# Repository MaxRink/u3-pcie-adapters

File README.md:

# U.3 PCIe adapters

Passive, PCIe 4.0 adapters for U.3 (SFF-TA-1001) NVMe drives, built around HPE P50230-B21 /
Samsung PM1735a drives that refuse U.2-wired hosts. KiCad projects, fabbed at JLCPCB or PCBWay.

## Designs

| Design | Boards | Status |
| --- | --- | --- |
| [**x16 / x8 U.3 cards**](designs/x16-u3-card/) | x8 card (2 drives), x16 card (4 drives, passive or with retimer), OCuLink cage board | cage board routed and DRC clean; cards in layout |
| [**Minisforum MS-01 / MS-A2**](designs/minisforum-u3/) | U.3-wired x4 card for the PCIe slot, U.3-wired replacement for the M.2 adapter | waiting on measurements of the stock adapters |
| [**Cooling shroud**](docs/thermal/) | 3D-printed high-temp shroud for the Jonsbo N5 | sized from the thermal analysis; model in progress |

<table>
<tr>
<td><br>Cage board, top</td>
<td><br>Cage board, bottom (OCuLink)</td>
</tr>
<tr>
<td><br>x8 card with 2 drives</td>
<td><br>x16 card with 4 drives</td>
</tr>
<tr>
<td><br>CFD: 4 drives x 25 W in line, 30 CFM</td>
<td><br>Hottest drive vs airflow (x8 / x16)</td>
</tr>
</table>

## Cooling in one paragraph

Each drive can draw ~25 W, and on the cards the drives sit in a row, so the air passes them one
after another. With 35 °C air coming in and a 70 °C case limit, the x8 card (2 drives) needs about
20 CFM and the x16 card (4 drives) about 30 CFM at ~150 Pa. That takes a 92x38 mm server-class
fan: it holds 2 drives at ~66 °C and 4 drives at ~71 °C (marginal; 3 mm shroud gaps or a 20 W
drive power state give margin). A 92x25 mm fan is not enough for either. Details, OpenFOAM
results and the calibrated model: [`docs/thermal/`](docs/thermal/).

## Layout

| Path | Contents |
| --- | --- |
| [`design-rules/`](design-rules/) | Shared PCIe 4.0 + JLCPCB/PCBWay rules: stackups, impedance, `.kicad_dru` DRC rules, KiCad starter templates, SI scripts |
| [`designs/x16-u3-card/`](designs/x16-u3-card/) | x16 / x8 slot cards for 2–4 U.3 drives, OCuLink cage board |
| [`designs/minisforum-u3/`](designs/minisforum-u3/) | U.3 adapters for Minisforum MS-01 / MS-A2 (PCIe x4 card, M.2-slot board) |
| [`tools/render/`](tools/render/) | Headless 3D renders of any `.kicad_pcb` (real copper/mask/silk, STEP parts, drives plugged in) |
| [`tools/thermal/`](tools/thermal/) | Analytical airflow/thermal model and OpenFOAM CFD case generator for the drive stack |
| [`docs/`](docs/) | Research notes, renders (`docs/img/`), thermal results (`docs/thermal/`) |

## Conventions

- One folder per design under `designs/`; one KiCad project per board inside it.
- Every board uses a template from `design-rules/templates/` and the custom rules in
  `design-rules/pcie4_jlc_pcbway.kicad_dru`. Change the rules there, not per board.
- Don't commit KiCad backups, `*.kicad_prl`, or fab output zips (see `.gitignore`);
  attach fab outputs to GitHub releases instead.
- Re-render a board after changing it (`tools/render/render.py`) so the README pictures match.

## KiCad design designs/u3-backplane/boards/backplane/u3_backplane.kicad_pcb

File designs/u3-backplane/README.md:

# Cabled U.3 backplane

A small NVMe backplane in the style of a Supermicro CSE-SAS-733TQ: U.3 drives stand on vertical receptacles,
every cable leaves sideways on the underside, and a host card in a PCIe x16 slot feeds it over SlimSAS 8i cables.
It is meant to sit flat in the top compartment of a Jonsbo N5 behind the two front 120 mm fans, with the drives
loaded from the top (so they can be swapped with the lid off), inside a printed cage.

| Board | Size | Drives | Cables | Files |
| --- | --- | --- | --- | --- |
| Backplane, 4 drives | 79.6 x 90.5 mm | 4 | 2 x SlimSAS 8i | `boards/backplane`, `fab/backplane` |
| Backplane, 6 drives | 119.6 x 90.5 mm (one 120 mm fan wide) | 6 | 3 x SlimSAS 8i | `boards/backplane6`, `fab/backplane6` |
| Host card, passive | 131 x 44 mm, PCIe x16 | 4 per card | 2 x SlimSAS 8i | `boards/host_passive`, `fab/host_passive` |

Two 6-drive modules side by side give 12 drives across both fans. That is 48 lanes: six 8i cables and three
x16 slots set to x4x4x4x4 (or a PCIe switch card).

All boards use the project's 6-layer rule set (JLC06161H-3313, 85 ohm pairs 0.157 / 0.152 mm, see
`design-rules/`). They are generated by the scripts in `gen/`; nothing is drawn by hand.

## Mechanics

Drawings: `docs/backplane_mech.svg`, `docs/backplane6_mech.svg`. Board-only STEP models are in `fab/*/`.

- Frame: seen from the drive side, origin top-left, x right, y down.
- Drive receptacles (Amphenol PSAS5F3130021TR, vertical, 8.15 mm tall) at x = 9.8 + 20 * i, y = 48.5, long axis
  along y, 20 mm pitch. Module pitch is 80 / 120 mm with 0.4 mm between boards.
- M3 holes: (3.2, 15.5), (W - 3.2, 15.5) and (36 + 40 * c, 86.3) for every drive pair c.
- Underside (all right angle, tallest part 13 mm, the cage keeps 15 mm clear):
  - y = 90.5 edge: one SlimSAS 8i per drive pair, centred at x = 15.8 + 40 * c.
  - y = 0 edge, left to right from the drive side: fan control in (1x4), 12 V in, 12 V out (Mini-Fit Jr 2x4),
    fan + fan control out (1x8).
- Slots between the drives let air through when the board stands upright. Lying flat they are not needed.

Assumed, not measured: the N5 top compartment has room for the cage (Max: "plenty of space"), and the drive's end
face sits about 6.5 mm above the board. The Amphenol drawing gives the 8.15 mm body height only.

## Electrical design

**Lanes.** One x4 link per drive, no lane crossings and exactly one via per net. Host transmit (PET) runs on L1
and drops to L6 behind the SlimSAS pads, drive transmit (PER) runs on L6. Lanes are 19 to 43 mm long. Pairs are
matched by the position of their vias, without serpentines (largest skew 0.004 mm, see
`fab/*/*-lengths.json`). 220 nF AC caps sit on the drive's lane 0 and 1 transmit pairs only
(SFF-TA-1001), S15 (HPT0) is grounded.

| SlimSAS connector | Port A (pins 1-18, host lanes 0-3) | Port B (pins 19-37, host lanes 4-7) |
| --- | --- | --- |
| first (left) | drive 1 | drive 0 |
| second | drive 3 | drive 2 |
| third (6-drive board) | drive 5 | drive 4 |

Sidebands follow SFF-9402: every port carries its own REFCLK, PERST#, CPRSNT#, CWAKE# and BP_TYPE (pulled low).
Cables must be the crossover type the spec describes (row A at one end is row B at the other).

**Power and hot plug.** 12 V enters on a PCIe 8-pin (Mini-Fit Jr) and is passed on to a second one for the next
module. Each drive has its own TPS259824 eFuse: about 3.9 A limit, soft start (10 nF on dV/dt), and it is only
switched on while a drive is present (PRSNT# or IfDet# low through a 74LVC1G00). A TPS3808 watches the drive's
12 V and releases the drive's PERST# about 125 ms after the rail is good, so a freshly inserted drive always sees
a proper reset. An empty bay is unpowered.

Daisy chain limit: a PCIe 8-pin is specified for 150 W. Four 25 W drives are 100 W, six are 150 W, so chain two
4-drive modules only with drives that stay under about 18 W each, and give every 6-drive module its own lead.

Host side of hot plug: the backplane is electrically safe to plug and pull. Whether the OS notices on its own
depends on the root port. A bifurcated consumer slot normally has no hot-plug slot capability, so use
`echo 1 > /sys/bus/pci/devices/<bdf>/remove` before pulling and `echo 1 > /sys/bus/pci/rescan` after inserting.
Boards that expose "PCIe hot plug" or Intel VMD for the slot handle it without that.

**Management.** One TCA9548A SMBus switch (address 0x71) gives every drive its own channel (channel = drive
number). One TCA9554 per drive pair (0x20, 0x21, 0x22) reads PRSNT#, IfDet#, IfDet2# and drives PWRDIS for both
drives (bits 0-3 even drive, 4-7 odd drive). The upstream bus is the 2-wire pair of port A on the first SlimSAS
connector; that port's PERST# also resets the switch. 3.3 V comes from an on-board LDO fed from 12 V (drive side,
above the fan header). L4 carries 12 V above the drives and to every eFuse and 3.3 V everywhere else.

**Fan.** The 1x8 header's pins 1-4 are a standard 4-pin fan header (GND, 12 V through a 1.1 A PTC, tach, PWM).
PWM and tach come from the "control in" header (mainboard fan header or the previous module), and PWM is passed
on by pins 5-8 to the next module. The 12 V pins of the control headers are not connected, so nothing is fed back
into the mainboard.

## Host card (passive)

PCIe x16 edge to two SlimSAS 8i, for a slot set to x4x4x4x4. The connectors sit on the underside at the top edge,
which keeps the lane order of the fingers. PET has one via, PER two. A 9DBL0442 buffer (bypass mode) gives each
port its own REFCLK, a TCA9546A (0x77) gives each port its own SMBus channel (channel 0 reaches the backplane's
switch), a TCA9554 (0x27) reads CPRSNT# and BP_TYPE of the four ports, PERST# goes to every port through 33 ohm
and the four CWAKE# lines join WAKE#. Trace length is 23 to 30 mm per lane.

A passive card plus a 0.5 m cable plus the backplane (19 to 43 mm) is past what PCIe 4.0 allows without
re-equalisation. Expect Gen3 to work and Gen4 to depend on the board and the cable. For Gen4, use a redriver or
retimer card.

**Redriver and retimer versions: not built (decided 2026-11-13).** For PCIe 4.0 a retimer card is bought instead
(see below). A redriver card (4 x DS160PR810) was analysed but not laid out: it does not re-time, so Gen4 over
0.5 m would stay uncertain. A retimer card cannot be laid out from public data, TI's public DS160PT801 datasheet
has no ball map.

## What to buy

Cables (one per drive pair): SlimSAS SFF-8654 8i to 8i, straight, 85 ohm, "PCIe 4.0", with sidebands, 0.5 m or
shorter.

| Cable | Notes |
| --- | --- |
| 3M 8ES8-1DF21-0.50 | reference-grade twinax, 85 ohm; the safest choice |
| 10Gtek CAB-8654/8654-8i-P-85 | "PCIe 4.0, 85 ohm, with sideband", 0.5 to 1 m, listed at about 15 USD (2026-11-13) |
| Delock 82303 (0.5 m) | SlimSAS 8i to 8i; impedance and sidebands not confirmed from the product page |

Avoid 100 ohm "SAS" cables and cables without sidebands: the drives would get no clock or reset.

Host card to buy instead of building one: a x16 to dual SlimSAS 8i **retimer** card, for example LR-LINK
LRNV9F24 or the C-Payne "SlimSAS PCIe gen4 host adapter x16" in its retimer version. Prices could not be read
from the vendor pages (LR-LINK sells on inquiry). Check before ordering that the card follows SFF-9402 on the
cable side (REFCLK and PERST# on every port); a card that only passes lanes will not bring up the drives.

## Cost estimate (JLCPCB, bare boards)

Not quoted live. Scaled from the project's quotes of 2026-11-13 for the same stackup (6 layers, ENIG, impedance
control, 0.2 mm vias: 141 to 188 USD for 5 to 10 cards of 190 to 310 mm length), where the fixed 6-layer charges
dominate:

| Board | 5 pcs | 10 pcs |
| --- | --- | --- |
| Backplane, 4 drives | about 105 USD | about 115 USD |
| Backplane, 6 drives | about 115 USD | about 130 USD |
| Host card (adds gold fingers and bevel) | about 125 USD | about 140 USD |

Parts per 4-drive backplane are roughly 45 USD (four receptacles about 4 USD each, two SlimSAS about 6 USD each,
four eFuses, the rest small), per host card roughly 30 USD. Shipping and tax are extra.

## Check before ordering

- Pin 1-3 = 12 V on the Mini-Fit Jr footprints was taken from the Molex numbering; check with a PSU cable.
- MCP1703A SOT-223 pinout (VIN, GND, VOUT) and the TPS259824 land pattern split are from memory or inferred.
- eFuse values (390 ohm ILIM, 2.2 nF ITIMER, 10 nF dV/dt) come from the datasheet formulas as remembered.
- LCSC numbers are filled in only where known; empty fields in the BOM need a part chosen.
- The 9DBL0442 and the eFuse are QFNs. Everything else is leaded or 0402 and larger; hot air works for all of it.
- The U.3 receptacle's seated drive height and the connector offset on the drive were not available.

## Regenerating

```
cd designs/u3-backplane/gen
ND=4 python3 bp.py        # 4-drive backplane (ND=6 for six), about 30 min
python3 host.py           # passive host card
cd .. && tools/outputs.sh backplane u3_backplane "Cabled U.3 backplane, 4 drives"        # backplane6 / u3_backplane6 for six
```

`tools/outputs.sh` runs the DRC (`tools/drc.py`) and writes the Gerber zip, BOM, CPL, the board-only STEP, the lane
length report and the mechanical drawing.

`STAGE=place` skips the low-speed router and gives a placement DRC in seconds. KiCad 7.0.11. A full run takes 20 to 30
minutes per board.

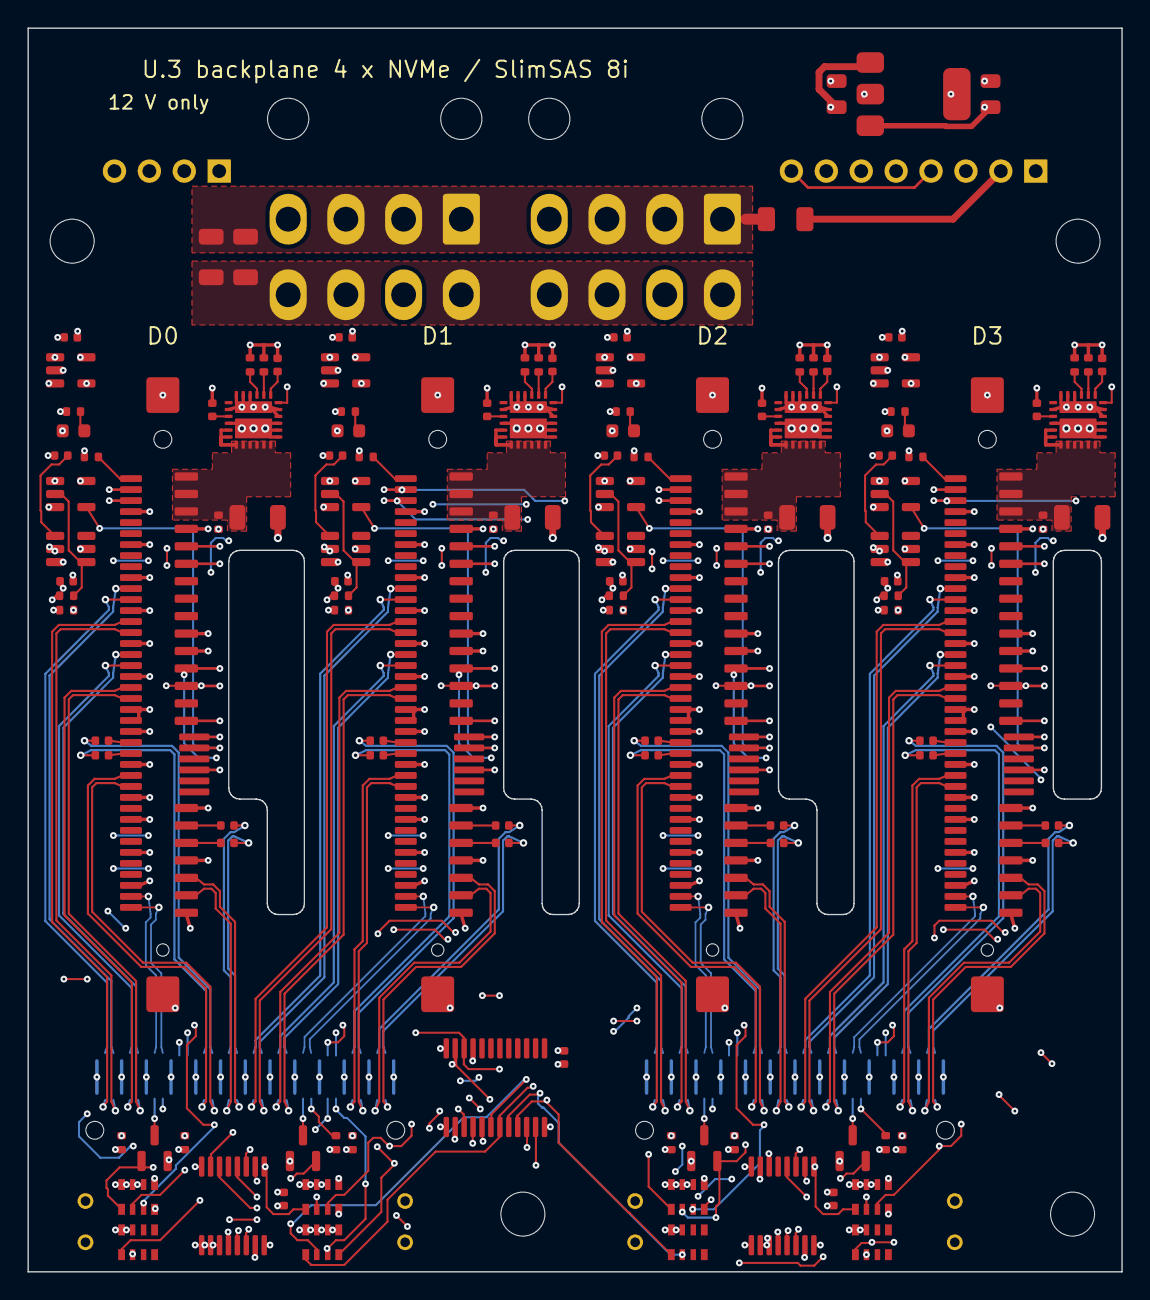
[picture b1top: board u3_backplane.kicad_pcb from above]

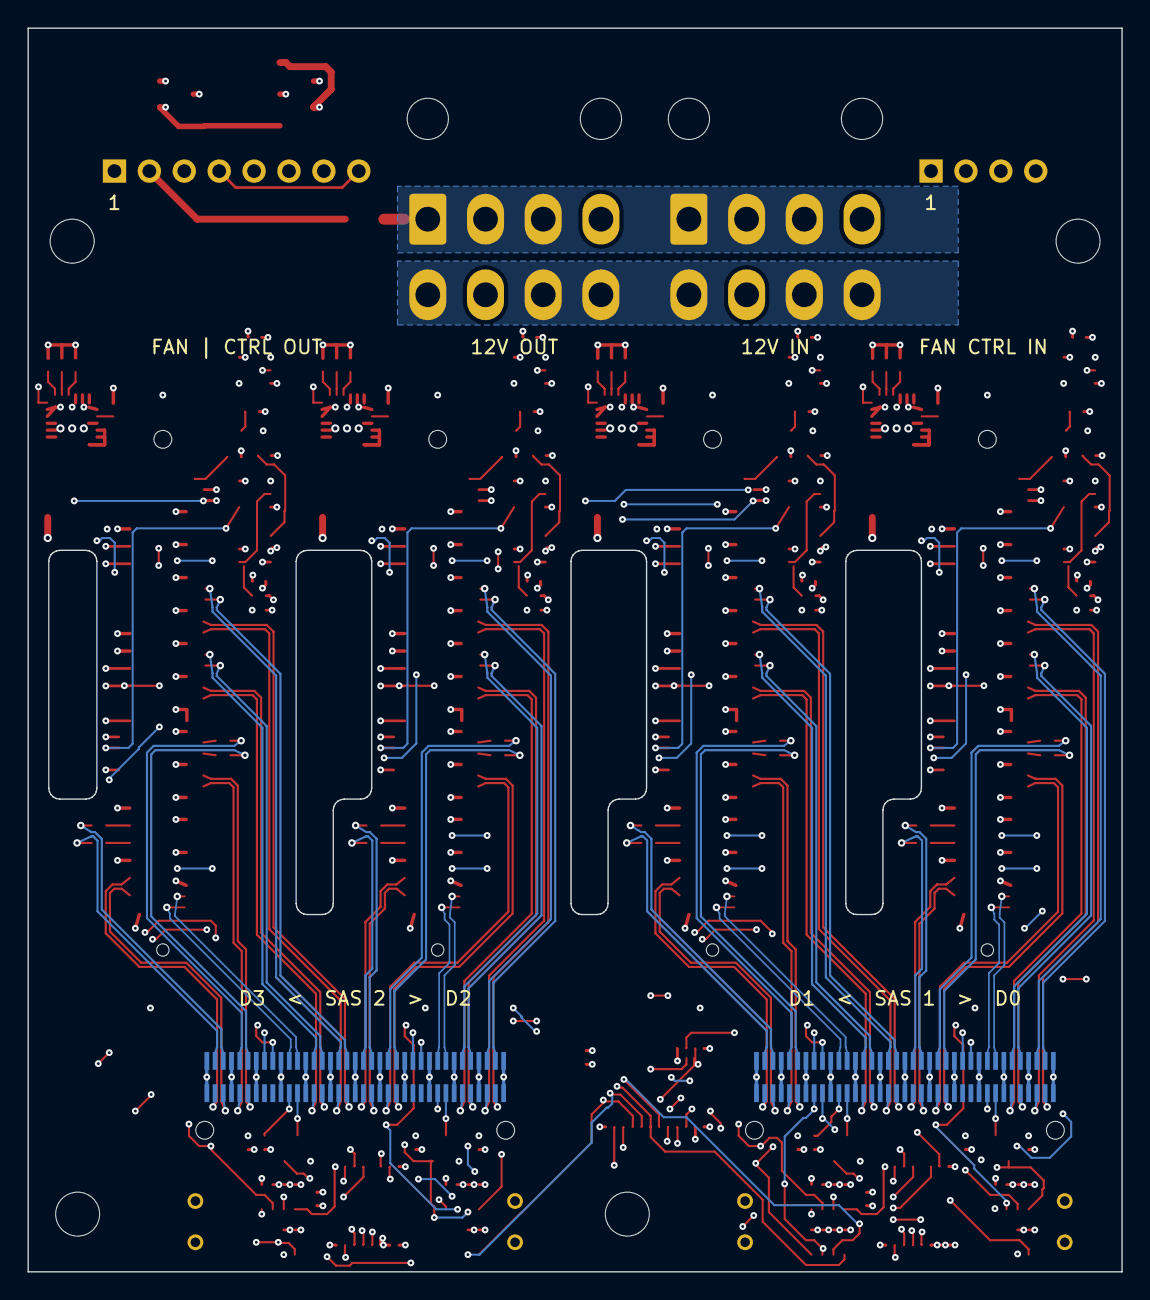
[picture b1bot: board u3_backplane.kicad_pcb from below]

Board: 6 copper layers, 79.6 x 90.5 mm, 134 parts (6 on the bottom side), 188 nets.

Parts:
C1, C2: 10uF 25V X5R; C_0805_2012Metric
C3, C10, C11, C121, C123, C221, C223, C321, C323, C421, C423: 100nF; C_0402_1005Metric
C5, C6, C120, C220, C320, C420: 22uF 25V X5R; C_1206_3216Metric
C101, C102, C111, C112, C201, C202, C211, C212, C301, C302, C311, C312, C401, C402, C411, C412: 220nF; C_0402_1005Metric
C122, C222, C322, C422: 22nF; C_0402_1005Metric
C124, C224, C324, C424: 2.2nF; C_0402_1005Metric
C125, C225, C325, C425: 10nF; C_0402_1005Metric
D1, D2, D3, D4: LED green 0603; LED_0603_1608Metric
D10, D20, D30, D40: BAT54A; SOT-23
F1: PTC 1206 1.1A 16V; Fuse_1206_3216Metric
H1, H2, H3, H4: M3; MountingHole_3.2mm_M3
J1, J2, J3, J4: PSAS5F3130021TR; Amphenol_PSAS5F313002_SFF-8639_U3_Vertical_SMD
J5, J6: U10A474240T; Amphenol_U10A474_SlimSAS_8i_SFF-8654_RA_SMD
J7: 12V IN PCIe 8-pin (Mini-Fit Jr 5569-08A2); Molex_Mini-Fit_Jr_5569-08A2_2x04_P4.20mm_Horizontal
J8: 12V OUT daisy chain (Mini-Fit Jr 5569-08A2); Molex_Mini-Fit_Jr_5569-08A2_2x04_P4.20mm_Horizontal
J9: FAN CTRL IN (from mainboard / previous module); PinHeader_1x04_P2.54mm_Horizontal
J10: FAN (pins 1-4) + FAN CTRL OUT (pins 5-8); PinHeader_1x08_P2.54mm_Horizontal
R11, R21, R31, R41: 24k 1%; R_0402_1005Metric
R12, R22, R32, R42: 1k 1%; R_0402_1005Metric
R13, R14, R17, R19, R23, R24, R27, R29, R33, R34, R37, R39, R43, R44, R47, R49: 10k; R_0402_1005Metric
R15, R25, R35, R45: 1k; R_0402_1005Metric
R16, R26, R36, R46: 100k; R_0402_1005Metric
R18, R28, R38, R48: 390R 1%; R_0402_1005Metric
RN1, RN2, RN3, RN4: 10k x4; R_Array_Convex_4x0603
RN11, RN12, RN13, RN14: 4.7k x4; R_Array_Convex_4x0603
U1: TCA9548APWR; TSSOP-24_4.4x7.8mm_P0.65mm
U3: MCP1703AT-3302E/DB; SOT-223-3_TabPin2
U5, U6: TCA9554PWR; TSSOP-16_4.4x5mm_P0.65mm
U11, U21, U31, U41: TPS3808G01DBVR; SOT-23-6
U12, U22, U32, U42: SN74LVC1G08DBVR; SOT-23-5
U13, U23, U33, U43: SN74LVC1G00DBVR; SOT-23-5
U14, U24, U34, U44: TPS259824ONRGER; TI_RGE0024M_VQFN-24_4x4mm_P0.5mm_SplitEP

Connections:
3V3_AUX: C2.1, C3.1, C10.1, C11.1, C121.1, C123.1, C221.1, C223.1, C321.1, C323.1, C421.1, C423.1, J1.E3, J2.E3, J3.E3, J4.E3, R13.1, R14.1, R15.1, R23.1, R24.1, R25.1, R33.1, R34.1, R35.1, R43.1, R44.1, R45.1, RN1.6, RN1.7, RN1.8, RN2.6, RN2.7, RN2.8, RN3.6, RN3.7, RN3.8, RN4.6, RN4.7, RN4.8, RN11.7, RN11.8, RN12.5, RN12.6, RN12.7, RN12.8, RN13.7, RN13.8, RN14.7, RN14.8, U1.1, U1.24, U3.3, U5.16, U6.1, U6.16, U11.6, U12.5, U13.5, U21.6, U22.5, U23.5, U31.6, U32.5, U33.5, U41.6, U42.5, U43.5
12V_IN: C1.1, C5.2, C6.2, F1.1, J7.1, J7.2, J7.3, J8.1, J8.2, J8.3, U3.1, U14.1, U14.2, U14.3, U14.16, U14.25, U24.1, U24.2, U24.3, U24.16, U24.25, U34.1, U34.2, U34.3, U34.16, U34.25, U44.1, U44.2, U44.3, U44.16, U44.25
D0C_PER0_N: C102.1, J1.S5
D0C_PER0_P: C101.1, J1.S6
D0C_PER1_N: C112.2, J1.S12
D0C_PER1_P: C111.2, J1.S13
D0_12V: C120.1, J1.P13, J1.P14, J1.P15, R11.2, U14.17, U14.18, U14.19, U14.20, U14.21, U14.22, U14.23, U14.24
D0_ACT_N: D1.1, J1.P11
D0_BPTYPE: J5.B26, R17.2
D0_CPRSNT_N: D10.3, J5.A30
D0_CT: C122.2, U11.4
D0_DPEN_N: J1.E25, R14.2
D0_DVDT: C125.1, U14.15
D0_EN: U13.4, U14.6
D0_IFDET2_N: J1.E6, RN1.3, U5.6
D0_IFDET_N: D10.2, J1.P4, RN1.2, U5.5, U13.2
D0_ILIM: R18.1, U14.8
D0_IMON: R19.1, U14.9
D0_ITMR: C124.1, U14.7
D0_LEDA: D1.2, R15.2
D0_PER0_N: C102.2, J5.B20
D0_PER0_P: C101.2, J5.B21
D0_PER1_N: C112.1, J5.B24
D0_PER1_P: C111.1, J5.B23
D0_PER2_N: J1.S20, J5.B33
D0_PER2_P: J1.S21, J5.B32
D0_PER3_N: J1.S26, J5.B36
D0_PER3_P: J1.S27, J5.B35
D0_PET0_N: J1.S3, J5.A20
D0_PET0_P: J1.S2, J5.A21
D0_PET1_N: J1.S10, J5.A24
D0_PET1_P: J1.S9, J5.A23
D0_PET2_N: J1.S18, J5.A33
D0_PET2_P: J1.S17, J5.A32
D0_PET3_N: J1.S24, J5.A36
D0_PET3_P: J1.S23, J5.A35
D0_PG: R13.2, U11.1, U12.2
D0_PRSNT_N: D10.1, J1.P10, RN1.1, U5.4, U13.1
D0_PRSTP: J5.A29, R16.2, U12.1
D0_PRST_N: J1.E5, U12.4
D0_PWRDIS: J1.P3, RN1.4, U5.7
D0_REFCLK_N: J1.E8, J5.B30
D0_REFCLK_P: J1.E7, J5.B29
D0_SCL: J1.E23, RN11.1, U1.5
D0_SDA: J1.E24, RN11.2, U1.4
D0_SNS: R11.1, R12.2, U11.5
D0_WAKE_N: J1.P1, J5.B27
D1C_PER0_N: C202.1, J2.S5
D1C_PER0_P: C201.1, J2.S6
D1C_PER1_N: C212.2, J2.S12
D1C_PER1_P: C211.2, J2.S13
D1_12V: C220.1, J2.P13, J2.P14, J2.P15, R21.2, U24.17, U24.18, U24.19, U24.20, U24.21, U24.22, U24.23, U24.24
D1_ACT_N: D2.1, J2.P11
D1_BPTYPE: J5.B8, R27.2
D1_CPRSNT_N: D20.3, J5.A12
D1_CT: C222.2, U21.4
D1_DPEN_N: J2.E25, R24.2
D1_DVDT: C225.1, U24.15
D1_EN: U23.4, U24.6
D1_IFDET2_N: J2.E6, RN2.3, U5.11
D1_IFDET_N: D20.2, J2.P4, RN2.2, U5.10, U23.2
D1_ILIM: R28.1, U24.8
D1_IMON: R29.1, U24.9
D1_ITMR: C224.1, U24.7
D1_LEDA: D2.2, R25.2
D1_PER0_N: C202.2, J5.B2
D1_PER0_P: C201.2, J5.B3
D1_PER1_N: C212.1, J5.B6
D1_PER1_P: C211.1, J5.B5
D1_PER2_N: J2.S20, J5.B15
D1_PER2_P: J2.S21, J5.B14
D1_PER3_N: J2.S26, J5.B18
D1_PER3_P: J2.S27, J5.B17
D1_PET0_N: J2.S3, J5.A2
D1_PET0_P: J2.S2, J5.A3
D1_PET1_N: J2.S10, J5.A6
D1_PET1_P: J2.S9, J5.A5
D1_PET2_N: J2.S18, J5.A15
D1_PET2_P: J2.S17, J5.A14
D1_PET3_N: J2.S24, J5.A18
D1_PET3_P: J2.S23, J5.A17
D1_PG: R23.2, U21.1, U22.2
D1_PRSNT_N: D20.1, J2.P10, RN2.1, U5.9, U23.1
D1_PRSTP: J5.A11, R26.2, U1.3, U22.1
D1_PRST_N: J2.E5, U22.4
D1_PWRDIS: J2.P3, RN2.4, U5.12
D1_REFCLK_N: J2.E8, J5.B12
D1_REFCLK_P: J2.E7, J5.B11
D1_SCL: J2.E23, RN12.1, U1.7
D1_SDA: J2.E24, RN12.2, U1.6
D1_SNS: R21.1, R22.2, U21.5
D1_WAKE_N: J2.P1, J5.B9
D2C_PER0_N: C302.1, J3.S5
D2C_PER0_P: C301.1, J3.S6
D2C_PER1_N: C312.2, J3.S12
D2C_PER1_P: C311.2, J3.S13
D2_12V: C320.1, J3.P13, J3.P14, J3.P15, R31.2, U34.17, U34.18, U34.19, U34.20, U34.21, U34.22, U34.23, U34.24
D2_ACT_N: D3.1, J3.P11
D2_BPTYPE: J6.B26, R37.2
D2_CPRSNT_N: D30.3, J6.A30
D2_CT: C322.2, U31.4
D2_DPEN_N: J3.E25, R34.2
D2_DVDT: C325.1, U34.15
D2_EN: U33.4, U34.6
D2_IFDET2_N: J3.E6, RN3.3, U6.6
D2_IFDET_N: D30.2, J3.P4, RN3.2, U6.5, U33.2
D2_ILIM: R38.1, U34.8
D2_IMON: R39.1, U34.9
D2_ITMR: C324.1, U34.7
D2_LEDA: D3.2, R35.2
D2_PER0_N: C302.2, J6.B20
D2_PER0_P: C301.2, J6.B21
D2_PER1_N: C312.1, J6.B24
D2_PER1_P: C311.1, J6.B23
D2_PER2_N: J3.S20, J6.B33
D2_PER2_P: J3.S21, J6.B32
D2_PER3_N: J3.S26, J6.B36
D2_PER3_P: J3.S27, J6.B35
D2_PET0_N: J3.S3, J6.A20
D2_PET0_P: J3.S2, J6.A21
D2_PET1_N: J3.S10, J6.A24
D2_PET1_P: J3.S9, J6.A23
D2_PET2_N: J3.S18, J6.A33
D2_PET2_P: J3.S17, J6.A32
D2_PET3_N: J3.S24, J6.A36
D2_PET3_P: J3.S23, J6.A35
D2_PG: R33.2, U31.1, U32.2
D2_PRSNT_N: D30.1, J3.P10, RN3.1, U6.4, U33.1
D2_PRSTP: J6.A29, R36.2, U32.1
D2_PRST_N: J3.E5, U32.4
D2_PWRDIS: J3.P3, RN3.4, U6.7
D2_REFCLK_N: J3.E8, J6.B30
D2_REFCLK_P: J3.E7, J6.B29
D2_SCL: J3.E23, RN13.1, U1.9
D2_SDA: J3.E24, RN13.2, U1.8
D2_SNS: R31.1, R32.2, U31.5
D2_WAKE_N: J3.P1, J6.B27
D3C_PER0_N: C402.1, J4.S5
D3C_PER0_P: C401.1, J4.S6
D3C_PER1_N: C412.2, J4.S12
D3C_PER1_P: C411.2, J4.S13
D3_12V: C420.1, J4.P13, J4.P14, J4.P15, R41.2, U44.17, U44.18, U44.19, U44.20, U44.21, U44.22, U44.23, U44.24
D3_ACT_N: D4.1, J4.P11
D3_BPTYPE: J6.B8, R47.2
D3_CPRSNT_N: D40.3, J6.A12
D3_CT: C422.2, U41.4
D3_DPEN_N: J4.E25, R44.2
D3_DVDT: C425.1, U44.15
D3_EN: U43.4, U44.6
D3_IFDET2_N: J4.E6, RN4.3, U6.11
D3_IFDET_N: D40.2, J4.P4, RN4.2, U6.10, U43.2
D3_ILIM: R48.1, U44.8
D3_IMON: R49.1, U44.9
D3_ITMR: C424.1, U44.7
D3_LEDA: D4.2, R45.2
D3_PER0_N: C402.2, J6.B2
D3_PER0_P: C401.2, J6.B3
D3_PER1_N: C412.1, J6.B6
D3_PER1_P: C411.1, J6.B5
D3_PER2_N: J4.S20, J6.B15
D3_PER2_P: J4.S21, J6.B14
D3_PER3_N: J4.S26, J6.B18
D3_PER3_P: J4.S27, J6.B17
D3_PET0_N: J4.S3, J6.A2
D3_PET0_P: J4.S2, J6.A3
D3_PET1_N: J4.S10, J6.A6
D3_PET1_P: J4.S9, J6.A5
D3_PET2_N: J4.S18, J6.A15
D3_PET2_P: J4.S17, J6.A14
D3_PET3_N: J4.S24, J6.A18
D3_PET3_P: J4.S23, J6.A17
D3_PG: R43.2, U41.1, U42.2
D3_PRSNT_N: D40.1, J4.P10, RN4.1, U6.9, U43.1
D3_PRSTP: J6.A11, R46.2, U42.1
D3_PRST_N: J4.E5, U42.4
D3_PWRDIS: J4.P3, RN4.4, U6.12
D3_REFCLK_N: J4.E8, J6.B12
D3_REFCLK_P: J4.E7, J6.B11
D3_SCL: J4.E23, RN14.1, U1.11
D3_SDA: J4.E24, RN14.2, U1.10
D3_SNS: R41.1, R42.2, U41.5
D3_WAKE_N: J4.P1, J6.B9
FAN_12V: F1.2, J10.2
FAN_PWM: J9.4, J10.4, J10.8
FAN_TACH: J9.3, J10.3
GND: C1.2, C2.2, C3.2, C5.1, C6.1, C10.2, C11.2, C120.2, C121.2, C122.1, C123.2, C124.2, C125.2, C220.2, C221.2, C222.1, C223.2, C224.2, C225.2, C320.2, C321.2, C322.1, C323.2, C324.2, C325.2, C420.2, C421.2, C422.1, C423.2, C424.2, C425.2, J1.E9, J1.E12, J1.E15, J1.E19, J1.E22, J1.MP, J1.P5, J1.P6, J1.P12, J1.S1, J1.S4, J1.S7, J1.S8, J1.S11, J1.S14, J1.S15, J1.S16, J1.S19, J1.S22, J1.S25, J1.S28, J2.E9, J2.E12, J2.E15, J2.E19, J2.E22, J2.MP, J2.P5, J2.P6, J2.P12, J2.S1, J2.S4, J2.S7, J2.S8, J2.S11, J2.S14, J2.S15, J2.S16, J2.S19, J2.S22, J2.S25, J2.S28, J3.E9, J3.E12, J3.E15, J3.E19, J3.E22, J3.MP, J3.P5, J3.P6, J3.P12, J3.S1, J3.S4, J3.S7, J3.S8, J3.S11, J3.S14, J3.S15, J3.S16, J3.S19, J3.S22, J3.S25, J3.S28, J4.E9, J4.E12, J4.E15, J4.E19, J4.E22, J4.MP, J4.P5, J4.P6, J4.P12, J4.S1, J4.S4, J4.S7, J4.S8, J4.S11, J4.S14, J4.S15, J4.S16, J4.S19, J4.S22, J4.S25, J4.S28, J5.A1, J5.A4, J5.A7, J5.A10, J5.A13, J5.A16, J5.A19, J5.A22, J5.A25, J5.A28, J5.A31, J5.A34, J5.A37, J5.B1, J5.B4, J5.B7, J5.B10, J5.B13, J5.B16, J5.B19, J5.B22, J5.B25, J5.B28, J5.B31, J5.B34, J5.B37, J5.SH, J6.A1, J6.A4, J6.A7, J6.A10, J6.A13, J6.A16, J6.A19, J6.A22, J6.A25, J6.A28, J6.A31, J6.A34, J6.A37, J6.B1, J6.B4, J6.B7, J6.B10, J6.B13, J6.B16, J6.B19, J6.B22, J6.B25, J6.B28, J6.B31, J6.B34, J6.B37, J6.SH, J7.5, J7.7, J7.8, J8.5, J8.7, J8.8, J9.1, J10.1, J10.5, R12.1, R16.1, R17.1, R18.2, R19.2, R22.1, R26.1, R27.1, R28.2, R29.2, R32.1, R36.1, R37.1, R38.2, R39.2, R42.1, R46.1, R47.1, R48.2, R49.2, RN1.5, RN2.5, RN3.5, RN4.5, U1.2, U1.12, U1.21, U3.2, U5.1, U5.2, U5.3, U5.8, U6.2, U6.3, U6.8, U11.2, U12.3, U13.3, U14.4, U14.5, U14.10, U14.11, U14.12, U14.14, U14.26, U21.2, U22.3, U23.3, U24.4, U24.5, U24.10, U24.11, U24.12, U24.14, U24.26, U31.2, U32.3, U33.3, U34.4, U34.5, U34.10, U34.11, U34.12, U34.14, U34.26, U41.2, U42.3, U43.3, U44.4, U44.5, U44.10, U44.11, U44.12, U44.14, U44.26
HOST_SCL: J5.A8, RN12.3, U1.22, U5.14, U6.14
HOST_SDA: J5.A9, RN12.4, U1.23, U5.15, U6.15

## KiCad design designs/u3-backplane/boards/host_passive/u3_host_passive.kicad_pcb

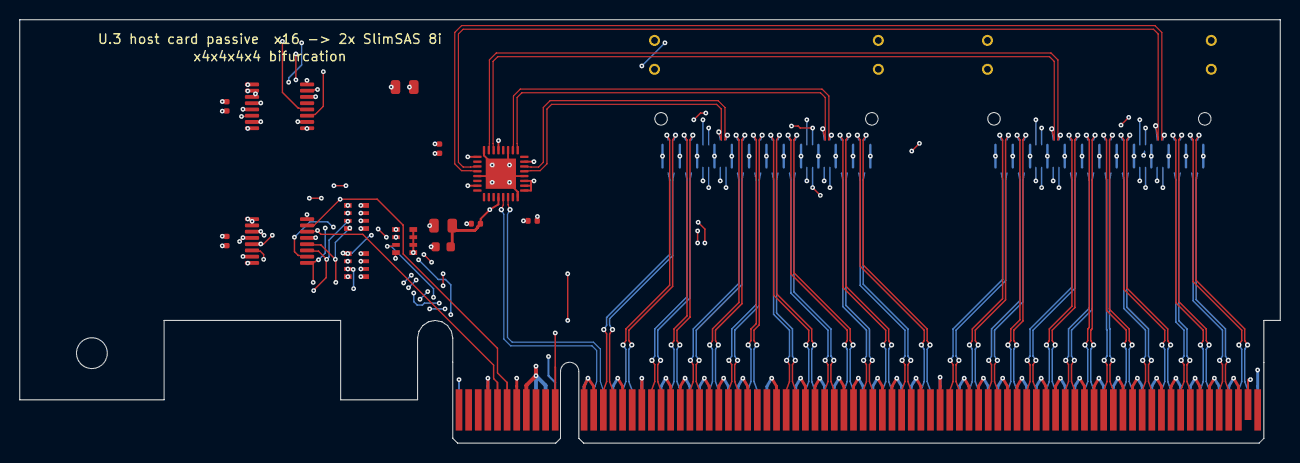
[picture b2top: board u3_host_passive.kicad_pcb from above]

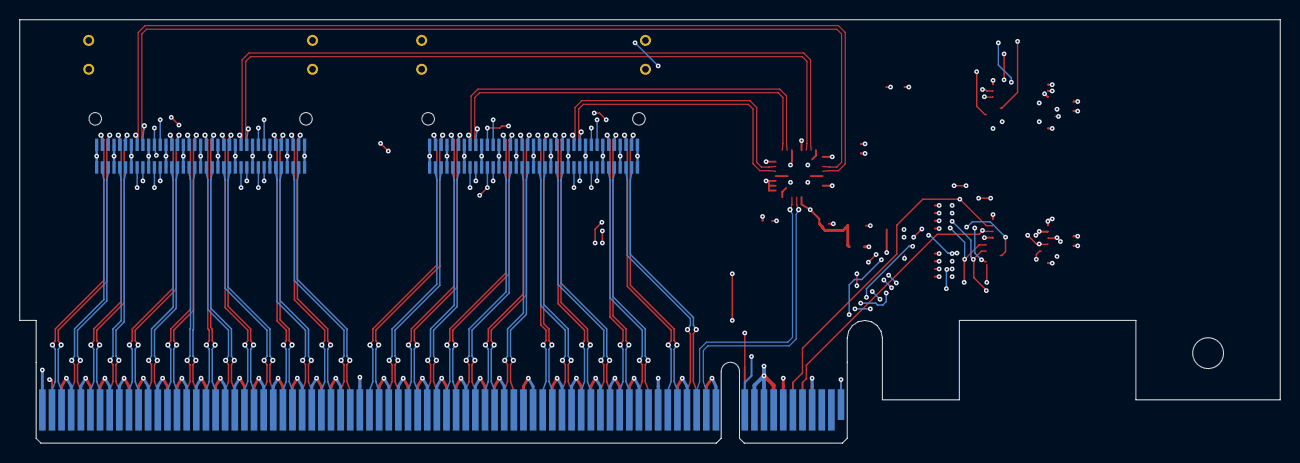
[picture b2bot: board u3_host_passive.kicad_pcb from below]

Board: 6 copper layers, 131.0 x 44.0 mm, 18 parts (2 on the bottom side), 102 nets.

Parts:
C1, C2, C4, C5, C6: 100nF; C_0402_1005Metric
C3, C7: 10uF 25V X5R; C_0805_2012Metric
FB1: ferrite 600R@100MHz; L_0603_1608Metric
H1: bracket; MountingHole_3.2mm_M3
J1: PCIe x16 edge; BUS_PCIexpress_x16
J2, J3: U10A474240T; Amphenol_U10A474_SlimSAS_8i_SFF-8654_RA_SMD
RN1, RN2: 4.7k x4; R_Array_Convex_4x0603
RN3: 33R x4; R_Array_Convex_4x0603
U1: 9DBL0442BKILF; VQFN-32-1EP_5x5mm_P0.5mm_EP3.15x3.15mm
U2: TCA9546APWR; TSSOP-16_4.4x5mm_P0.65mm
U3: TCA9554PWR; TSSOP-16_4.4x5mm_P0.65mm

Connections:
3V3: C1.2, C2.2, C3.1, C4.1, C5.1, FB1.1, J1.A9, J1.A10, J1.B8, RN1.5, RN1.6, RN1.7, RN1.8, RN2.5, RN2.6, RN2.7, RN2.8, U1.9, U1.10, U1.11, U1.15, U1.25, U1.31, U2.1, U2.2, U2.13, U2.16, U3.1, U3.2, U3.3, U3.16
3V3_A: C6.2, C7.2, FB1.2, U1.4, U1.21
GND: C1.1, C2.1, C3.2, C4.2, C5.2, C6.1, C7.1, J1.A4, J1.A12, J1.A15, J1.A18, J1.A20, J1.A23, J1.A24, J1.A27, J1.A28, J1.A31, J1.A34, J1.A37, J1.A38, J1.A41, J1.A42, J1.A45, J1.A46, J1.A49, J1.A51, J1.A54, J1.A55, J1.A58, J1.A59, J1.A62, J1.A63, J1.A66, J1.A67, J1.A70, J1.A71, J1.A74, J1.A75, J1.A78, J1.A79, J1.A82, J1.B4, J1.B7, J1.B12, J1.B13, J1.B16, J1.B18, J1.B21, J1.B22, J1.B25, J1.B26, J1.B29, J1.B32, J1.B35, J1.B36, J1.B39, J1.B40, J1.B43, J1.B44, J1.B47, J1.B49, J1.B52, J1.B53, J1.B56, J1.B57, J1.B60, J1.B61, J1.B64, J1.B65, J1.B68, J1.B69, J1.B72, J1.B73, J1.B76, J1.B77, J1.B80, J2.A1, J2.A4, J2.A7, J2.A10, J2.A13, J2.A16, J2.A19, J2.A22, J2.A25, J2.A28, J2.A31, J2.A34, J2.A37, J2.B1, J2.B4, J2.B7, J2.B10, J2.B13, J2.B16, J2.B19, J2.B22, J2.B25, J2.B28, J2.B31, J2.B34, J2.B37, J2.SH, J3.A1, J3.A4, J3.A7, J3.A10, J3.A13, J3.A16, J3.A19, J3.A22, J3.A25, J3.A28, J3.A31, J3.A34, J3.A37, J3.B1, J3.B4, J3.B7, J3.B10, J3.B13, J3.B16, J3.B19, J3.B22, J3.B25, J3.B28, J3.B31, J3.B34, J3.B37, J3.SH, U1.8, U1.12, U1.19, U1.24, U1.29, U1.33, U2.8, U3.8
P0_BPTYPE: J2.A8, U3.9
P0_CPRSNT_N: J2.B12, U3.4
P0_PERST_N: J2.B11, RN3.1
P0_SCL: J2.B8, RN1.2, U2.5
P0_SDA: J2.B9, RN1.1, U2.4
P1_BPTYPE: J2.A26, U3.10
P1_CPRSNT_N: J2.B30, U3.5
P1_PERST_N: J2.B29, RN3.2
P1_SCL: J2.B26, RN1.4, U2.7
P1_SDA: J2.B27, RN1.3, U2.6
P2_BPTYPE: J3.A8, U3.11
P2_CPRSNT_N: J3.B12, U3.6
P2_PERST_N: J3.B11, RN3.3
P2_SCL: J3.B8, RN2.2, U2.10
P2_SDA: J3.B9, RN2.1, U2.9
P3_BPTYPE: J3.A26, U3.12
P3_CPRSNT_N: J3.B30, U3.7
P3_PERST_N: J3.B29, RN3.4
P3_SCL: J3.B26, RN2.4, U2.12
P3_SDA: J3.B27, RN2.3, U2.11
PCIE_RST_N: J1.A11, RN3.5, RN3.6, RN3.7, RN3.8, U2.3
PCIE_WAKE_N: J1.B11, J2.A9, J2.A27, J3.A9, J3.A27
PER0_N: J1.A17, J2.A3
PER0_P: J1.A16, J2.A2
PER1_N: J1.A22, J2.A6
PER1_P: J1.A21, J2.A5
PER2_N: J1.A26, J2.A15
PER2_P: J1.A25, J2.A14
PER3_N: J1.A30, J2.A18
PER3_P: J1.A29, J2.A17
PER4_N: J1.A36, J2.A21
PER4_P: J1.A35, J2.A20
PER5_N: J1.A40, J2.A24
PER5_P: J1.A39, J2.A23
PER6_N: J1.A44, J2.A33
PER6_P: J1.A43, J2.A32
PER7_N: J1.A48, J2.A36
PER7_P: J1.A47, J2.A35
PER8_N: J1.A53, J3.A3
PER8_P: J1.A52, J3.A2
PER9_N: J1.A57, J3.A6
PER9_P: J1.A56, J3.A5
PER10_N: J1.A61, J3.A15
PER10_P: J1.A60, J3.A14
PER11_N: J1.A65, J3.A18
PER11_P: J1.A64, J3.A17
PER12_N: J1.A69, J3.A21
PER12_P: J1.A68, J3.A20
PER13_N: J1.A73, J3.A24
PER13_P: J1.A72, J3.A23
PER14_N: J1.A77, J3.A33
PER14_P: J1.A76, J3.A32
PER15_N: J1.A81, J3.A36
PER15_P: J1.A80, J3.A35
PET0_N: J1.B15, J2.B3
PET0_P: J1.B14, J2.B2
PET1_N: J1.B20, J2.B6
PET1_P: J1.B19, J2.B5
PET2_N: J1.B24, J2.B15
PET2_P: J1.B23, J2.B14
PET3_N: J1.B28, J2.B18
PET3_P: J1.B27, J2.B17
PET4_N: J1.B34, J2.B21
PET4_P: J1.B33, J2.B20
PET5_N: J1.B38, J2.B24
PET5_P: J1.B37, J2.B23
PET6_N: J1.B42, J2.B33
PET6_P: J1.B41, J2.B32
PET7_N: J1.B46, J2.B36
PET7_P: J1.B45, J2.B35
PET8_N: J1.B51, J3.B3
PET8_P: J1.B50, J3.B2
PET9_N: J1.B55, J3.B6
PET9_P: J1.B54, J3.B5
PET10_N: J1.B59, J3.B15
PET10_P: J1.B58, J3.B14
PET11_N: J1.B63, J3.B18
PET11_P: J1.B62, J3.B17
PET12_N: J1.B67, J3.B21
PET12_P: J1.B66, J3.B20
PET13_N: J1.B71, J3.B24
PET13_P: J1.B70, J3.B23
PET14_N: J1.B75, J3.B33
PET14_P: J1.B74, J3.B32
PET15_N: J1.B79, J3.B36
PET15_P: J1.B78, J3.B35
PRSNT_N: J1.A1, J1.B81
REFCLK0_N: J2.A12, U1.14
REFCLK0_P: J2.A11, U1.13
REFCLK1_N: J2.A30, U1.18
REFCLK1_P: J2.A29, U1.17
REFCLK2_N: J3.A12, U1.23
REFCLK2_P: J3.A11, U1.22
REFCLK3_N: J3.A30, U1.28
REFCLK3_P: J3.A29, U1.27
REFCLK_IN_N: J1.A14, U1.6
REFCLK_IN_P: J1.A13, U1.5
SMCLK: J1.B5, U2.14, U3.14
SMDAT: J1.B6, U2.15, U3.15
